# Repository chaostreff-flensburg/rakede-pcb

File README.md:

# ctfl-rakete-pcb

Converting this sticker desing into a PCB that lights up its flame and lighthouse top from the bottom side using some LEDs and a coin cell battery.

## Implementing the colors

Produce the PCBs with **red solder mask** and **white Silkscreen**.

| color | objects | pcb layers present | notes |
| --- | --- | --- | --- |
| white | background |  | considering the background to be transparent |
| white | w_flame | F.Cu, F.Silkscreen |  |
| yellow | y_flame, y_light | none | blank FR4 should give a nice translucent yellow |
| red | r_flame | F.Mask | only red solder mask should give a nice translucent red |
| red | r_tower, r_top, r_roof | F.Mask, f.Cu | with the copper underneath, the red solder mask should appear darker than at the flame |
| light grey | w_base, w_tower | F.Cu, F.Silkscreen |  |
| dark grey | g_base | F.Cu | not differentiated from black outlines |
| black | b_contours, b_name | F.Cu, F.Mask | only copper coated with tin should give a nice contouring contrast |

### Extracting solder mask geometry (F.Mask) from the complete SVG file

In KiCAD the solder mask is expressed as an exclusion mask from the usually all present solder mask coverage.
Meaning that you define geometry where you want solder mask NOT to be.

So the gemonetry we import into KiCAD has to be the negative of the red parts of our logo.

Additionally the solder mask has to back up the silkscreen so that negative image also has to include our white parts.

I concrete terms we need to perform the following steps on our yource vector grapfics to get the desired F.Mask geometry:
1. Delete the yellow lighthous part at the top because it is clipped by all surrounding parts and itself does not clip any other.
1. Combine the white and the red flame part into one.
1. Subtract the yellow flame part from the formerly combined rest of the flame.
1. Also subtract the dark grey socket part from the remaining flame.
1. Combine all remaining red and white parts.
1. Subtract the black outlines which shall poke through the solder mask and the silk screen. Now we have our positive image of the solder mask we want (plus the outline which we also want for positioning).
1. Duplicate the outline and move the duplicate below our solder mask positive.
1. Subtract the positive from the duplicate of the outline.
1. Save as new SVG file (`F.Mask.svg`)
1. Now you can import the SVG file to the appropriate layer in the pcb layout while scaling it by **1.85**.

## Part sourcing

| cnt THT | cnt THT-uC | cnt SMD | reference | title | reichelt.de | mouser.de |
| --- | --- | --- | --- | --- | --- | --- |
| 1 | 1 | 1 | BT1 | battery clip | [KZH 20SMD](https://www.reichelt.de/knopfzellenclip-fuer-20-mm-smd-kzh-20smd-p56574.html) | [534-3034](https://www.mouser.de/ProductDetail/Keystone-Electronics/3034?qs=LDXARy4xNQtGYr6pIAv90A%3D%3D) |
| 1 | 1 | 1 | SW1 | power switch | [SS SMD402](https://www.reichelt.de/schiebeschalter-1x-um-liegend-smd-ss-smd402-p112181.html) | [MSS-102545-14A-V-SMT](https://www.mouser.de/ProductDetail/CUI-Devices/MSS-102545-14A-V-SMT?qs=DRkmTr78QARl%2FtwuH8uRQg%3D%3D) |
| 0 | 1 | 1 | U1 | microcontroller | [ATTINY212](https://www.reichelt.de/8-bit-attiny-avr-risc-mikrocontroller-2-kb-20-mhz-soic-8-attiny212-ssn-p335520.html) | [ATTINY212-SSN](https://www.mouser.de/ProductDetail/Microchip-Technology/ATTINY212-SSN?qs=3HJ2avRr9PJX8cJeG3zkDw%3D%3D) |
| 0 | 0 | 14 | D? | SMD LEDs | - | [859-LTW-220DS5](https://www.mouser.de/ProductDetail/Lite-On/LTW-220DS5?qs=xb8aMrBSZRKaoLOPaZYE%252BQ%3D%3D) or [XIASONGXIN LIGHT - Side SMD 0805 (choose warm white)](https://de.aliexpress.com/item/32890300371.html) |
| 7 | 7 | 0 | D? | 5mm LEDs | [EVERLIGHT 334-15/X1C5-6QSA/EU](https://www.reichelt.de/led-5-mm-bedrahtet-warmweiss-7150-mcd-50--led-el-5-7150ww-p164207.html) | [941-C512AWNSCZ0B0152](https://www.mouser.de/ProductDetail/Cree-LED/C512A-WNS-CZ0B0152?qs=xEJ61ozf1a3Ja%252B55bf1fHw%3D%3D) |
| 0 | 1 | 1 | J1 | programming header (break off 3 of 50) | - | [437-8018305040001101](https://www.mouser.de/ProductDetail/Preci-dip/801-83-050-40-001101?qs=KBM%2FMdeLKegYqxBCoh54QQ%3D%3D) |
| 0 | 1 | 1 | C1 | 0805 capacitor 100 nF | - | [80-C0805C104J5R](https://www.mouser.de/ProductDetail/KEMET/C0805C104J5RACTU?qs=gbgtKHXraGH15GhoNPXHBg%3D%3D) |
| 0 | 1 | 1 | C3 | 0805 capacitor 1 uF | - | [963-UMK212B7105KG-T](https://www.mouser.de/ProductDetail/TAIYO-YUDEN/UMK212B7105KG-T?qs=PzICbMaShUdi76GLXMVYcA%3D%3D) |

## Default firmware

The directory `defaultFirmware` holds an Arduino sketch that is meant to be used with the [megaTinyCore](https://github.com/SpenceKonde/megaTinyCore) board support package for Arduino and can then be uploaded using a programmer like [SerialUPDI](https://github.com/wagiminator/AVR-Programmer/tree/master/SerialUPDI_Programmer), e.g. the [Adafruit UPDI Friend](https://learn.adafruit.com/adafruit-updi-friend).

Make sure to select the correct Chip in Arduino under `Tools -> Chip -> ATtiny212`, the correct Programmer under `Tools -> Programmer -> SerialUPDI - 230400 baud` (probably, depending on what you have) as well as the correct clock source under `Tools -> Clock -> "5 MHz internal"`

The logo on the PCB and the blinking pattern are based on the [lighthouse Kalkgrund](https://www.deutsche-leuchtfeuer.de/ostsee/kalkgrund.html).

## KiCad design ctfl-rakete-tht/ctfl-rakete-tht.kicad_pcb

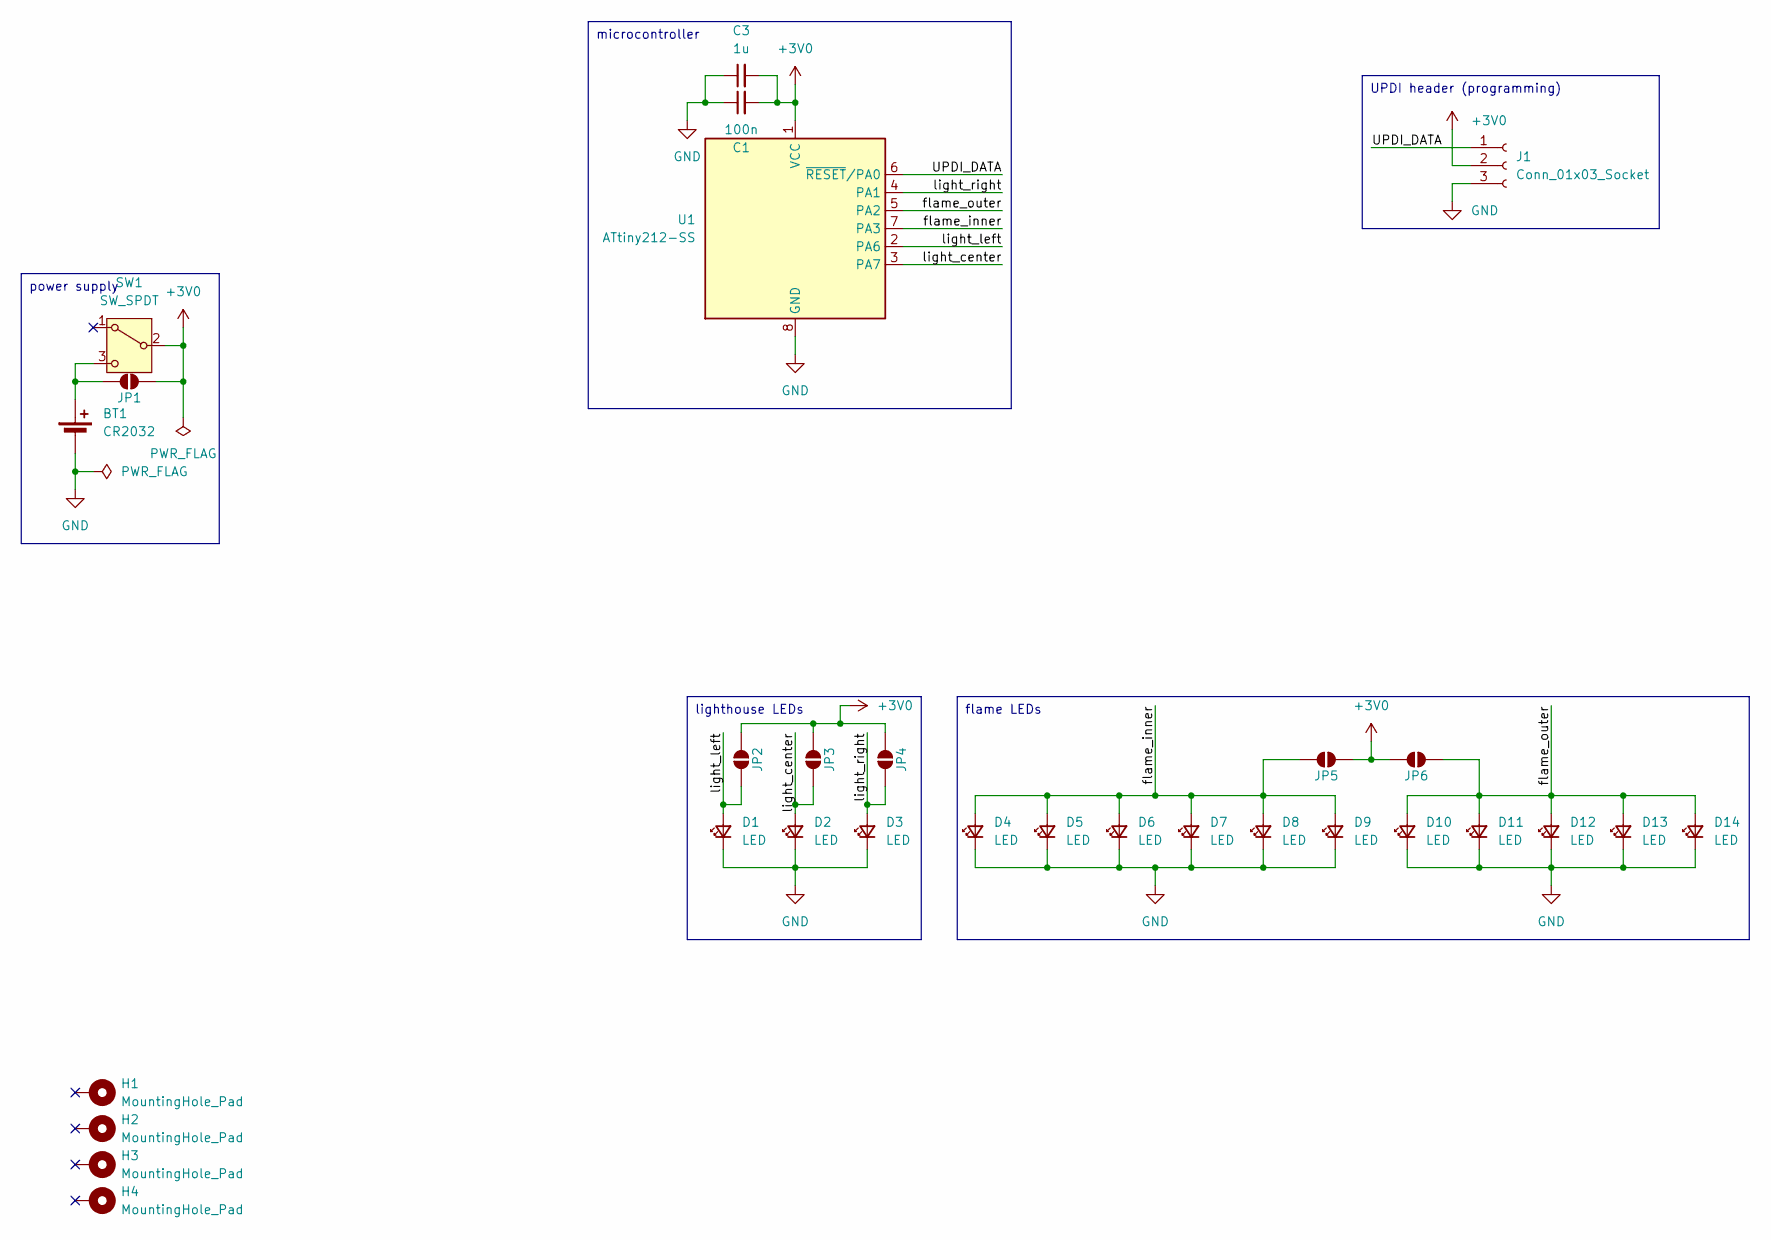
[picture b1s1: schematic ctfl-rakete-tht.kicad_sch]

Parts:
BT1: CR2032; BatteryHolder_Multicomp_BC-2001_1x2032
C1: 100n; C_0805_2012Metric_Pad1.18x1.45mm_HandSolder
C3: 1u; C_0805_2012Metric_Pad1.18x1.45mm_HandSolder
D1, D2, D3, D4, D5, D10, D11: LED; LED_combo_0805_5mmSMD_HandSolder
D6, D7, D8, D9, D12, D13, D14: LED; LED_0805_SMD_HandSolder
H1, H2, H3, H4: MountingHole_Pad; wire_pad
J1: Conn_01x03_Socket; PinSocket_1x03_P2.54mm_Horizontal_SMD
JP1, JP2, JP3, JP4, JP5, JP6: SolderJumper_2_Open; SolderJumper-2_P1.3mm_Open_RoundedPad1.0x1.5mm
SW1: SW_SPDT; SW_SPDT_ESP4020
U1: ATtiny212-SS; SOIC-8_3.9x4.9mm_P1.27mm

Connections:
+3V0: C1.2, C3.2, J1.2, JP1.2 (B), JP2.2 (B), JP3.2 (B), JP4.2 (B), JP5.2 (B), JP6.2 (B), SW1.2 (B), U1.1 (VCC)
/UPDI_DATA: J1.1, U1.6 (~RESET/PA0)
/flame_inner: D4.2 (A), D5.2 (A), D6.2 (A), D7.2 (A), D8.2 (A), D9.2 (A), JP5.1 (A), U1.7 (PA3)
/flame_outer: D10.2 (A), D11.2 (A), D12.2 (A), D13.2 (A), D14.2 (A), JP6.1 (A), U1.5 (PA2)
/light_center: D2.2 (A), JP3.1 (A), U1.3 (PA7)
/light_left: D1.2 (A), JP2.1 (A), U1.2 (PA6)
/light_right: D3.2 (A), JP4.1 (A), U1.4 (PA1)
GND: BT1.2 (-), C1.1, C3.1, D1.1 (K), D2.1 (K), D3.1 (K), D4.1 (K), D5.1 (K), D6.1 (K), D7.1 (K), D8.1 (K), D9.1 (K), D10.1 (K), D11.1 (K), D12.1 (K), D13.1 (K), D14.1 (K), J1.3, U1.8 (GND)
unnamed: BT1.1 (+), JP1.1 (A), SW1.3 (C)

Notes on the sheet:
flame LEDs
UPDI header (programming)
microcontroller
lighthouse LEDs
power supply

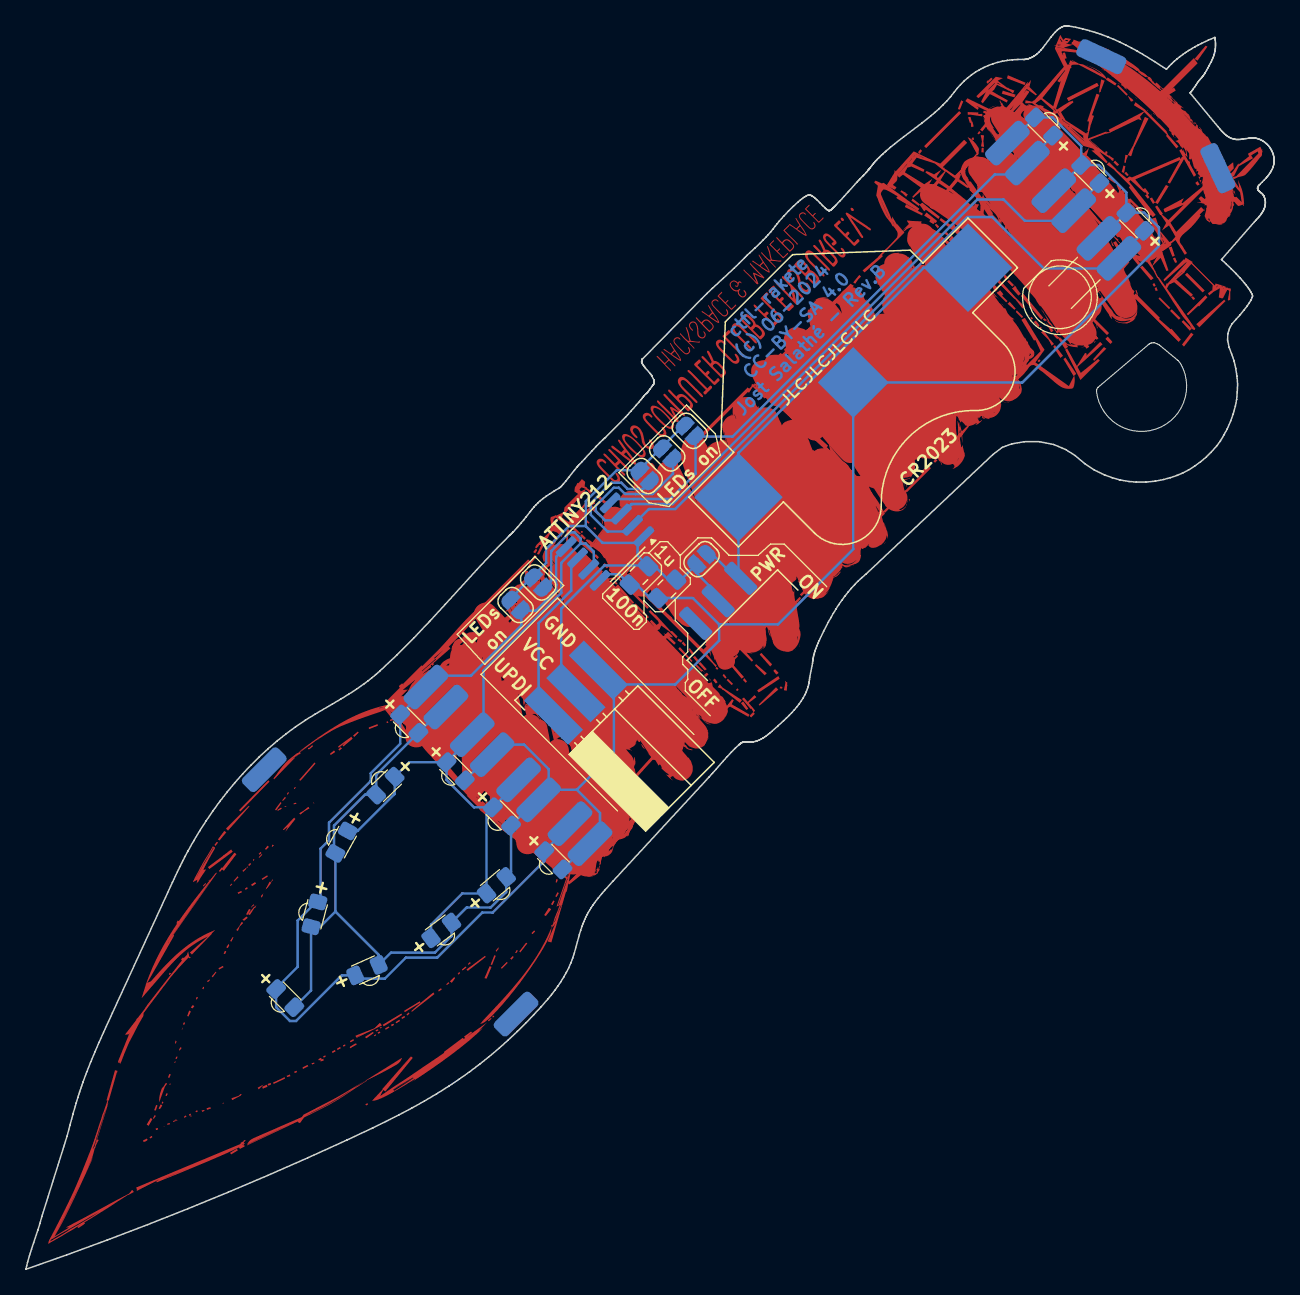
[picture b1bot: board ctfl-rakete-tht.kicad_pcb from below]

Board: 2 copper layers, 99.6 x 99.2 mm, 30 parts (30 on the bottom side), 9 nets.

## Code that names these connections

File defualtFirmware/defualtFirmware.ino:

const int PIN_LIGHT_R = PIN_PA1;
const int PIN_FLAME_O = PIN_PA2;
const int PIN_FLAME_I = PIN_PA3;
const int PIN_LIGHT_L = PIN_PA6; // no PWM
const int PIN_LIGHT_C = PIN_PA7;

void setup() {
  pinMode(PIN_LIGHT_R, OUTPUT);
  pinMode(PIN_FLAME_O, OUTPUT);
  pinMode(PIN_FLAME_I, OUTPUT);
  pinMode(PIN_LIGHT_L, OUTPUT);
  pinMode(PIN_LIGHT_C, OUTPUT);

  // digitalWrite(PIN_LIGHT_R, HIGH);
  // delay(500);
  // digitalWrite(PIN_LIGHT_R, LOW);

  // digitalWrite(PIN_LIGHT_C, HIGH);
  // delay(500);
  // digitalWrite(PIN_LIGHT_C, LOW);

  // digitalWrite(PIN_LIGHT_L, HIGH);
  // delay(500);
  // digitalWrite(PIN_LIGHT_L, LOW);

  // digitalWrite(PIN_FLAME_I, HIGH);
  // delay(500);
  // digitalWrite(PIN_FLAME_I, LOW);

  // digitalWrite(PIN_FLAME_O, HIGH);
  // delay(500);
  // digitalWrite(PIN_FLAME_O, LOW);
}

void runLight() {
  const int intervalMs = 33;
  const int restartIntervalMs = 3000;

  static unsigned long next = 0;
  static unsigned long nextRestart = 0;
  static int state = 0;

  if (millis() > next) {
    switch(state) {
    case 0:
      digitalWrite(PIN_LIGHT_R, HIGH);
      state = 1;
      break;

    case 1:
      digitalWrite(PIN_LIGHT_R, LOW);
      digitalWrite(PIN_LIGHT_C, HIGH);
      state = 2;
      break;

    case 2:
      digitalWrite(PIN_LIGHT_C, LOW);
      digitalWrite(PIN_LIGHT_L, HIGH);
      state = 3;
      break;

    case 3:
      digitalWrite(PIN_LIGHT_L, LOW);
      state = 4;
      break;

    default:
      break;
    }

    if (millis() > nextRestart) {
      state = 0;
      nextRestart += restartIntervalMs;
    }

    next += intervalMs;
  }
}

void runFlame() {
  const uint8_t pwmDim = 192, pwmBright = 255;
  const int intervalMs = 33;

  static unsigned long next = 0;
  static int state = 0;

  if (millis() > next) {
    switch (state) {
    case 0:
      analogWrite(PIN_FLAME_I, pwmDim);
      analogWrite(PIN_FLAME_O, pwmDim);
      state = 1;
      break;

    case 1:
      analogWrite(PIN_FLAME_I, pwmBright);
      analogWrite(PIN_FLAME_O, pwmDim);
      state = 2;
      break;

    case 2:
    default:
      analogWrite(PIN_FLAME_I, pwmDim);
      analogWrite(PIN_FLAME_O, pwmBright);
      state = 0;
      break;
    }

    next += intervalMs;
  }
}

void loop() {
  runLight();
  runFlame();
}

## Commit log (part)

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2024-03-05 added CC BY-SA 4.0 license file
2024-03-05 changed license file content to plain text
2024-03-10 added sticker svg and empty kicad project
2024-03-10 removed lock files from kicad project - we don't want to track those
2024-03-10 add png version of original logo
2024-03-10 added a max size frame into pcb design
2024-03-10 merged a lot of single paths into large paths to simplify the svg import into KiCad
2024-03-10 added ideas about how to implement the different colors of the original design on PCB
2024-03-19 added dedicate svg files for pcb layers Edge.Cuts, F.Cu and F.Mask, but they need additional fiducials...
2024-04-23 added silkscreen svg file and imported all into layout
2024-05-04 added some part sourcing links for battery clip and power switch and added some design ideas
2024-05-04 added some markers for future LED positions
2024-05-04 added symbols for battery clip, ATtiny, power switch and one LED
2024-05-04 corrected markdown table syntax
2024-05-07 created combo footprint for 0805 SMD or 5mm standard LED
2024-05-07 added ATTINY212 to part sources list
2024-05-07 added LED symbols and a bunch of wires and replaced ATTINY85 with ATTINY212 symbol
2024-05-10 added new kicad autosave file to gitignore
2024-05-10 added UPDI header and associated R and C
2024-05-10 added pwr_flags to satisfy ERC in schematic
2024-05-10 reimported graphics into layout scaled to 139 percent for optimum 100x100 mm PCB limit usage (the original size was too slim for the battery clip)
2024-05-10 optimized polarity marking placement on LED footprint
2024-05-10 moved LED footprints to their locations
2024-05-10 removed some solder mask from the bottom side where the LEDs shall shine
2024-05-10 optimized switch connections
2024-05-10 added pre-defined track sizes
2024-05-10 placed other components and started routing
2024-05-11 added footprint for power switch
2024-05-11 finished layout for revision A
2024-05-11 added renders of Rev.A to README.md
2024-05-11 removed the svg from README.md
2024-05-14 replaced in-flame LED footprints with 0805-only version and reoriented them
2024-05-14 added footprint for hanging wire solder points
2024-05-17 added hanging wire solder points and updated renders
2024-05-21 added reichelt.de reference to 5 mm LEDs
2024-05-25 added PDF plot of schematics
2024-05-25 added fabrication files
2024-05-28 added a second decoupling capacitor with 1 uF to the Controller supply
2024-05-30 updated to use design with new name 'Chaos Computer Club Flensburg E.V.'
2024-05-31 added parts from mouser.de
2024-06-01 added sourcing links to mouser.de for the remaining parts
2024-06-01 added and updated meta data of schematics and layout pages
2024-06-02 repaired mouser.de links
2024-06-10 updated F.Mask.svg and added instructions on how to generate this geometry following #1
2024-06-10 close #1: replaced F.Mask in layout with revised geometry as per previous commit and extended B.Mask around ATtiny212 label
2024-06-12 added first version of defaultFirmware arduino sketch
2024-06-12 small correction in README.md
2024-06-24 added notes about more suitable lighthous animation timing to defaultFirmware
2024-06-24 WIP: added new still incomplete footprint for horizontal SMD pin header
2024-06-24 WIP: started work on changing the programming header footprint to a more suitable 3 pin variant
2024-06-24 added a loop to Edge.Cuts so that people can clip the pcb to a lanyard
2024-06-24 close #3: replaced old programming header with a 1x3 horizontal SMD pin socket footprint (don't let the 3D model of it fool you)
2024-06-24 changed programming header part in BOM
2024-06-24 corrected slightly embarassing typo...
2024-06-24 updated schematics pdf
2024-06-25 added logo script to mask and silkscreen layer so that it is more legible and added a placeholder for JLCPCBs order number
2024-06-25 changed revision marking to Rev.B
2024-07-02 changed animation source code of defaultFirmware.ino to mimic the lighting pattern of lighthous Norderney
2024-07-09 slightly adjusted animation
2024-07-15 updated part listw ith amounts for different variants
2024-07-15 fixed parts list syntax in README.md
2024-07-15 another small fix for README.md
2024-07-15 exchanged mouser reference to battery clip for a better one that is a little cheaper and currently more available
2025-03-02 added photos for assembly manual and started work on german assembly manual
2025-03-06 added photo montage for tht-LED with uC mixed build
2025-04-22 finished german instructions for level 1
2025-04-22 added remark about sparse battery clip soldering
2025-12-28 added excellent smd soldering tips from blinkyparts
2025-12-28 Rechtschreibkorrektur
2026-01-05 added current consumption traces for Li-Ion voltage range on default firmware
    Measured with Rhode&Schwarz NGC103 lab PSU
2026-01-09 changed animation timing in defaultFirmware.ino to 'Leuchtturm Kalkgrund'
    see https://www.deutsche-leuchtfeuer.de/ostsee/kalkgrund.html
2026-01-09 reworked defaultFirmware.ino to support global dimming
2026-01-10 fixed bug where micros() was overflowing but nextFrame in animateFlame() was not
2026-01-10 added remarks about chip and clock selection to README.md
2026-01-10 added global dimming in relation to supply voltage to keep light output and current consumption nearly constant above a certain voltage
2026-01-13 Added hint about programmer selection to README.md
2026-01-26 added discharge recording of a LIR2032 supplying the current firmware
2026-01-28 added recording of LIR2032 discharge cycle with enabled under voltage lockout (MCU shutdown below 2.8V)
    The test failled because apparentlly the MCU did correctly shut down at 2.8 V but it held the GPIO states (all LEDs on) which should not be the case.
2026-01-28 Added LED shutoff before going to sleep on undervoltage and fixed GPIO initiallization
2026-01-28 reduced ADC reference to 1.5 V so that 2.4 V can actually be detected
2026-01-29 reduced voltage dependant global dimming brightness
    from 200 to 80
2026-01-30 added recording of LIR2032H discharge cycle with enabled under voltage lockout that completely works
    with the reduced global brightness from ed443e1, this now yields a run time of about 7.5 hours
2026-01-30 Rename battery name in recording from LIR2032 to LIR2032H
2026-02-03 added comments about different current consumptions to defaultFirmware.ino
2026-02-11 Made hard coded brightness values depend on global max brightness definitions
2026-02-13 improved VCC dimming curve
2026-02-20 idea for fixing flame freeze bug
    The frame index for animateFlame() is now derived from nowUs argument by dividing by FRAMETIME_US instead of counting nest frame start time up by FRAMETIME_US when micros() returns a lager value.
    This should fix the flame animation freeze that occurred on some micros() overflows.
2026-03-03 fixed stupid typo
2026-03-03 switched to Li-Ion cutoff voltage
